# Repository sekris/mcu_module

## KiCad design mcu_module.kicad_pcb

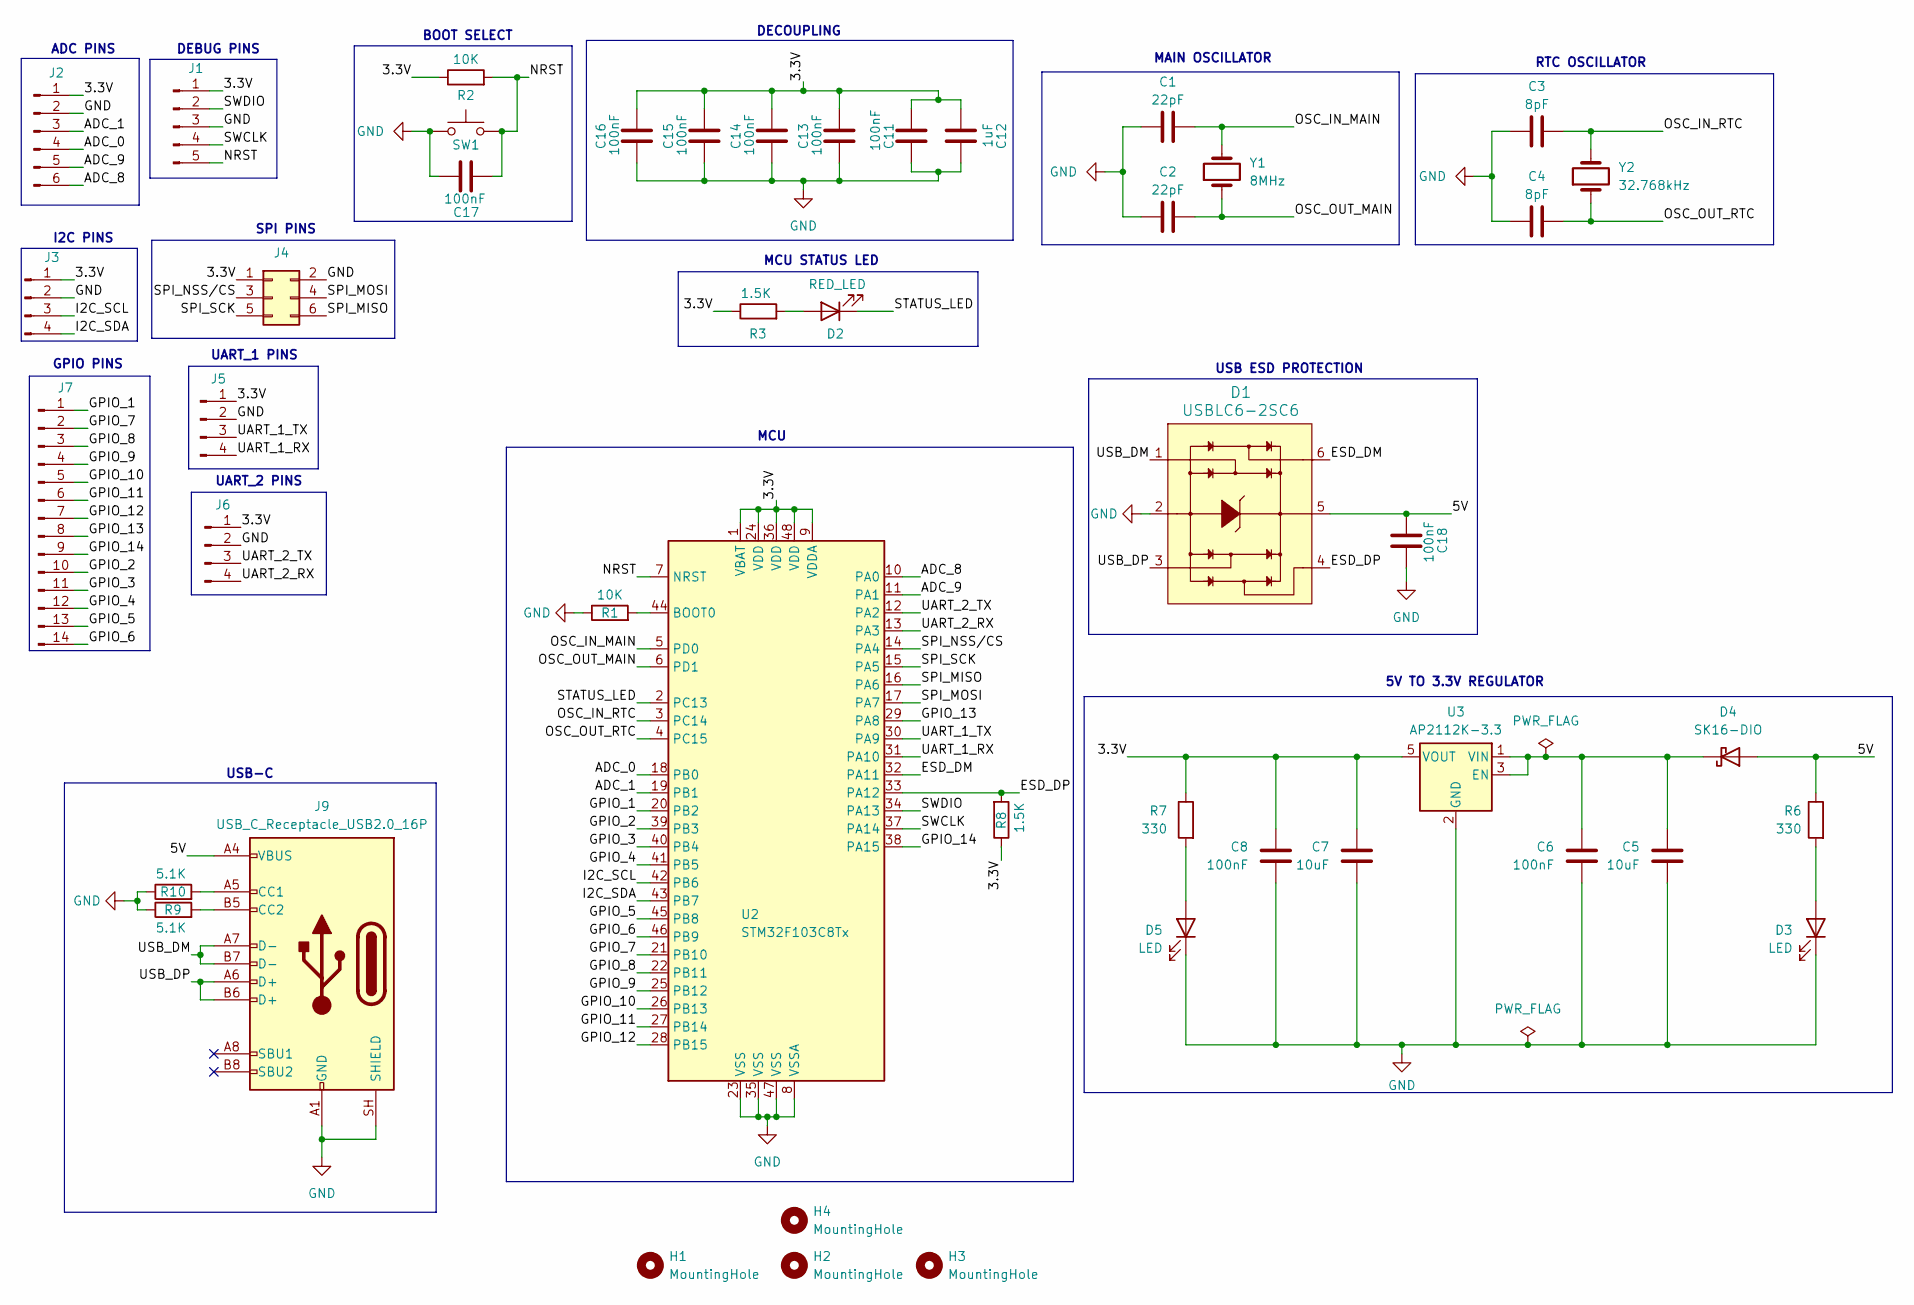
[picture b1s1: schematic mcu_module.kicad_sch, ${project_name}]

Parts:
C1, C2: 22pF; C_0805_2012Metric_Pad1.18x1.45mm_HandSolder
C3, C4: 8pF; C_0805_2012Metric_Pad1.18x1.45mm_HandSolder
C5, C7: 10uF; C_0805_2012Metric_Pad1.18x1.45mm_HandSolder
C6, C8, C11, C13, C14, C15, C16, C17, C18: 100nF; C_0805_2012Metric_Pad1.18x1.45mm_HandSolder
C12: 1uF; C_0805_2012Metric_Pad1.18x1.45mm_HandSolder
D1: USBLC6-2SC6; SOT23-6L; MPN USBLC6-2SC6; Digi-Key_PN 497-5235-1-ND
D2: RED_LED; LED_0805_2012Metric_Pad1.15x1.40mm_HandSolder
D3, D5: LED; LED_0805_2012Metric_Pad1.15x1.40mm_HandSolder
D4: SK16-DIO; P25_DO-214AC_SMA
H1, H2, H3, H4: MountingHole; MountingHole_2.2mm_M2
J1: Conn_01x05_Pin; PinSocket_1x05_P2.54mm_Vertical
J2: Conn_01x06_Pin; PinSocket_1x06_P2.54mm_Vertical
J3, J5, J6: Conn_01x04_Pin; PinSocket_1x04_P2.54mm_Vertical
J4: Conn_02x03_Odd_Even; PinSocket_2x03_P2.54mm_Vertical
J7: Conn_01x14_Pin; PinSocket_1x14_P2.54mm_Vertical
J9: USB_C_Receptacle_USB2.0_16P; USB_C_Receptacle_HRO_TYPE-C-31-M-12
R1, R2: 10K; R_0805_2012Metric_Pad1.20x1.40mm_HandSolder
R3, R8: 1.5K; R_0805_2012Metric_Pad1.20x1.40mm_HandSolder
R6, R7: 330; R_0805_2012Metric_Pad1.20x1.40mm_HandSolder
R9, R10: 5.1K; R_0805_2012Metric_Pad1.20x1.40mm_HandSolder
SW1: SW_Push; SW_SPST_CK_RS282G05A3
U2: STM32F103C8Tx; LQFP-48_7x7mm_P0.5mm
U3: AP2112K-3.3; SOT-23-5
Y1: 8MHz; XTAL_HC49P488W43L1085T450H368
Y2: 32.768kHz; XTAL_AB26T_32_768KHZ

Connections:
/3.3V: C7.1, C8.1, C11.2, C12.2, C13.2, C14.2, C15.2, C16.2, J1.1, J2.1, J3.1, J4.1, J5.1, J6.1, R2.1, R3.1, R7.1, R8.1, U2.1 (VBAT), U2.9 (VDDA), U2.24 (VDD), U2.36 (VDD), U2.48 (VDD), U3.5 (VOUT)
/5V: C18.1, D1.5, D4.2 (A), J9.A4 (VBUS), J9.A9 (VBUS), J9.B4 (VBUS), J9.B9 (VBUS), R6.1
/ADC_0: J2.4, U2.18 (PB0)
/ADC_1: J2.3, U2.19 (PB1)
/ADC_8: J2.6, U2.10 (PA0)
/ADC_9: J2.5, U2.11 (PA1)
/ESD_DM: D1.6, U2.32 (PA11)
/ESD_DP: D1.4, R8.2, U2.33 (PA12)
/GPIO_1: J7.1, U2.20 (PB2)
/GPIO_2: J7.10, U2.39 (PB3)
/GPIO_3: J7.11, U2.40 (PB4)
/GPIO_4: J7.12, U2.41 (PB5)
/GPIO_5: J7.13, U2.45 (PB8)
/GPIO_6: J7.14, U2.46 (PB9)
/GPIO_7: J7.2, U2.21 (PB10)
/GPIO_8: J7.3, U2.22 (PB11)
/GPIO_9: J7.4, U2.25 (PB12)
/GPIO_10: J7.5, U2.26 (PB13)
/GPIO_11: J7.6, U2.27 (PB14)
/GPIO_12: J7.7, U2.28 (PB15)
/GPIO_13: J7.8, U2.29 (PA8)
/GPIO_14: J7.9, U2.38 (PA15)
/I2C_SCL: J3.3, U2.42 (PB6)
/I2C_SDA: J3.4, U2.43 (PB7)
/NRST: C17.1, J1.5, R2.2, SW1.2, U2.7 (NRST)
/OSC_IN_MAIN: C1.2, U2.5 (PD0), Y1.2
/OSC_IN_RTC: C3.2, U2.3 (PC14), Y2.2
/OSC_OUT_MAIN: C2.2, U2.6 (PD1), Y1.1
/OSC_OUT_RTC: C4.2, U2.4 (PC15), Y2.1
/SPI_MISO: J4.6, U2.16 (PA6)
/SPI_MOSI: J4.4, U2.17 (PA7)
/SPI_NSS/CS: J4.3, U2.14 (PA4)
/SPI_SCK: J4.5, U2.15 (PA5)
/STATUS_LED: D2.1 (K), U2.2 (PC13)
/SWCLK: J1.4, U2.37 (PA14)
/SWDIO: J1.2, U2.34 (PA13)
/UART_1_RX: J5.4, U2.31 (PA10)
/UART_1_TX: J5.3, U2.30 (PA9)
/UART_2_RX: J6.4, U2.13 (PA3)
/UART_2_TX: J6.3, U2.12 (PA2)
/USB_DM: D1.1, J9.A7 (D-), J9.B7 (D-)
/USB_DP: D1.3, J9.A6 (D+), J9.B6 (D+)
GND: C1.1, C2.1, C3.1, C4.1, C5.2, C6.2, C7.2, C8.2, C11.1, C12.1, C13.1, C14.1, C15.1, C16.1, C17.2, C18.2, D1.2, D3.1 (K), D5.1 (K), J1.3, J2.2, J3.2, J4.2, J5.2, J6.2, J9.A1 (GND), J9.A12 (GND), J9.B1 (GND), J9.B12 (GND), J9.SH (SHIELD), R1.1, R9.1, R10.1, SW1.1, U2.8 (VSSA), U2.23 (VSS), U2.35 (VSS), U2.47 (VSS), U3.2 (GND)
unnamed: D2.2 (A), R3.2
unnamed: D3.2 (A), R6.2
unnamed: C5.1, C6.1, D4.1 (K), U3.1 (VIN), U3.3 (EN)
unnamed: D5.2 (A), R7.2
unnamed: J9.A5 (CC1), R10.2
unnamed: J9.B5 (CC2), R9.2
unnamed: R1.2, U2.44 (BOOT0)

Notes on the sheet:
MAIN OSCILLATOR
DEBUG PINS
SPI PINS
BOOT SELECT
DECOUPLING
I2C PINS
MCU STATUS LED
RTC OSCILLATOR
USB ESD PROTECTION
MCU
5V TO 3.3V REGULATOR
GPIO PINS
UART_2 PINS
UART_1 PINS
USB-C
ADC PINS

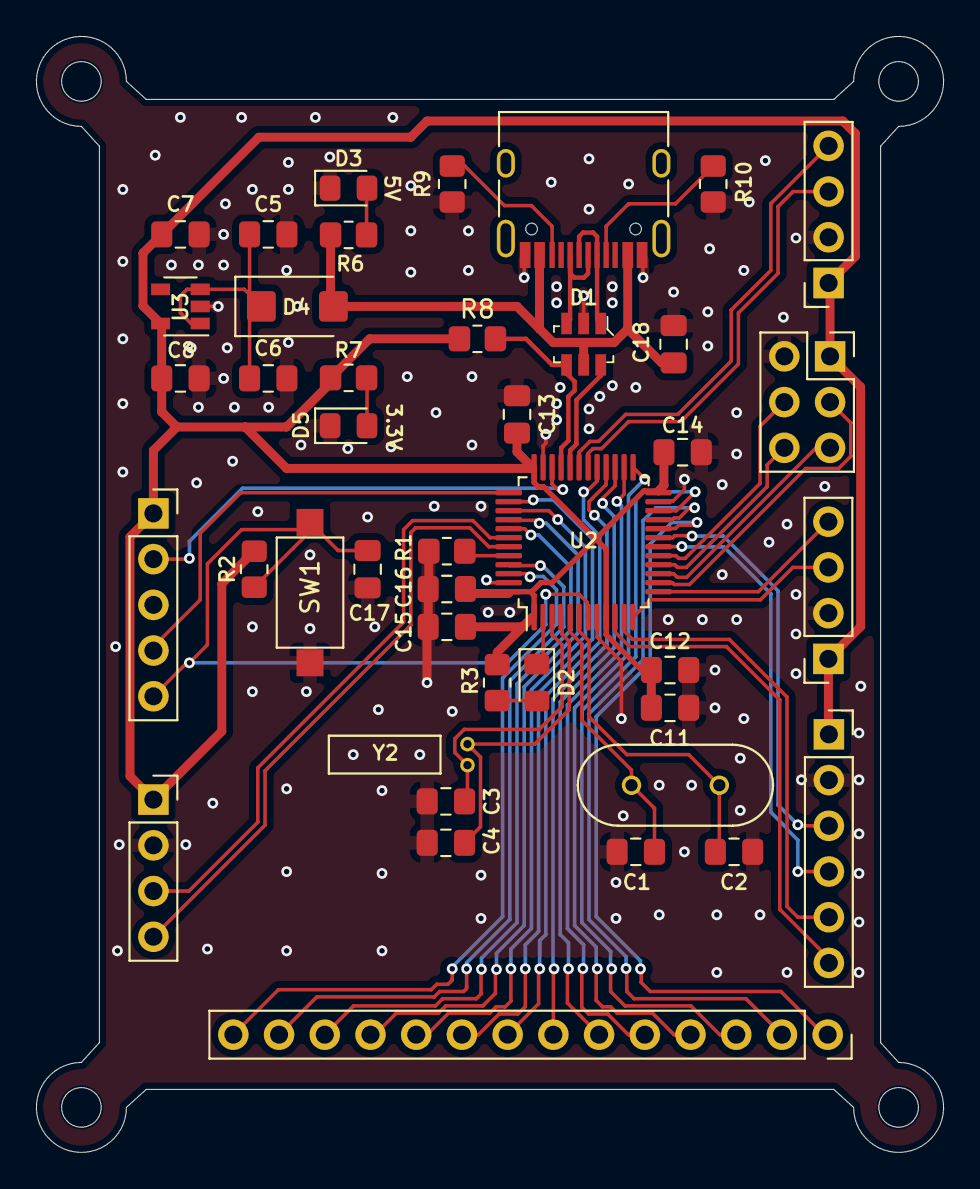
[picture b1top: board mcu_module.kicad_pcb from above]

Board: 2 copper layers, 50.4 x 62.0 mm, 46 parts (0 on the bottom side), 50 nets.
